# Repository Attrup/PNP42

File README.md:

# PNP42
Custom parts and PCBs used in the PNP42 prototype. 

# See It In Action
Time lapse of the prototype assembling the test-PCB:

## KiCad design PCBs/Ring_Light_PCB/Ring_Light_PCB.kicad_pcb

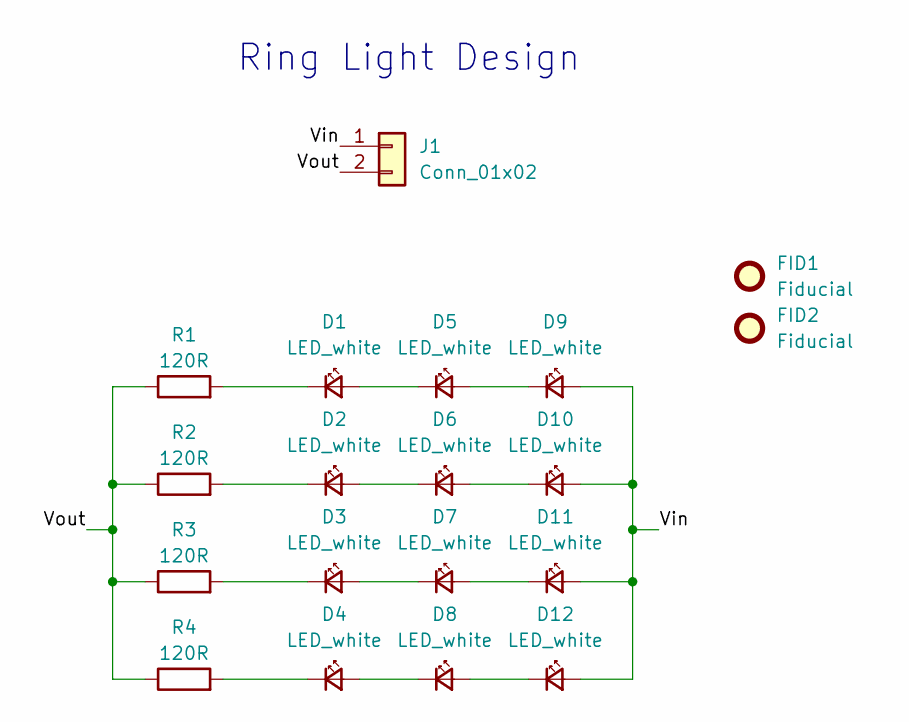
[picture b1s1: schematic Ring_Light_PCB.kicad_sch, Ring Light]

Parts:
D1, D2, D3, D4, D5, D6, D7, D8, D9, D10, D11, D12: LED_white; LED_D5.0mm
FID1, FID2: Fiducial; Fiducial_1mm_Mask2mm
J1: Conn_01x02; PinHeader_1x02_P2.54mm_Vertical
R1, R2, R3, R4: 120R; R_0805_2012Metric_Pad1.20x1.40mm_HandSolder

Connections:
/Vin: D9.2 (A), D10.2 (A), D11.2 (A), D12.2 (A), J1.1
/Vout: J1.2, R1.1, R2.1, R3.1, R4.1
unnamed: D1.1 (K), R1.2
unnamed: D1.2 (A), D5.1 (K)
unnamed: D2.1 (K), R2.2
unnamed: D2.2 (A), D6.1 (K)
unnamed: D3.1 (K), R3.2
unnamed: D3.2 (A), D7.1 (K)
unnamed: D4.1 (K), R4.2
unnamed: D4.2 (A), D8.1 (K)
unnamed: D5.2 (A), D9.1 (K)
unnamed: D6.2 (A), D10.1 (K)
unnamed: D7.2 (A), D11.1 (K)
unnamed: D8.2 (A), D12.1 (K)

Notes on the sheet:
Ring Light Design

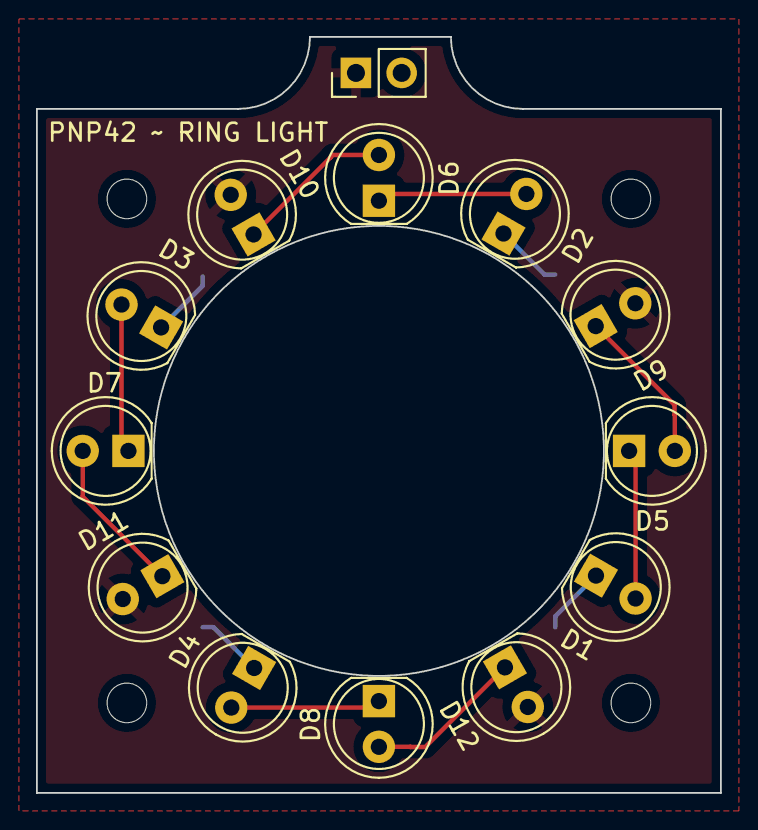
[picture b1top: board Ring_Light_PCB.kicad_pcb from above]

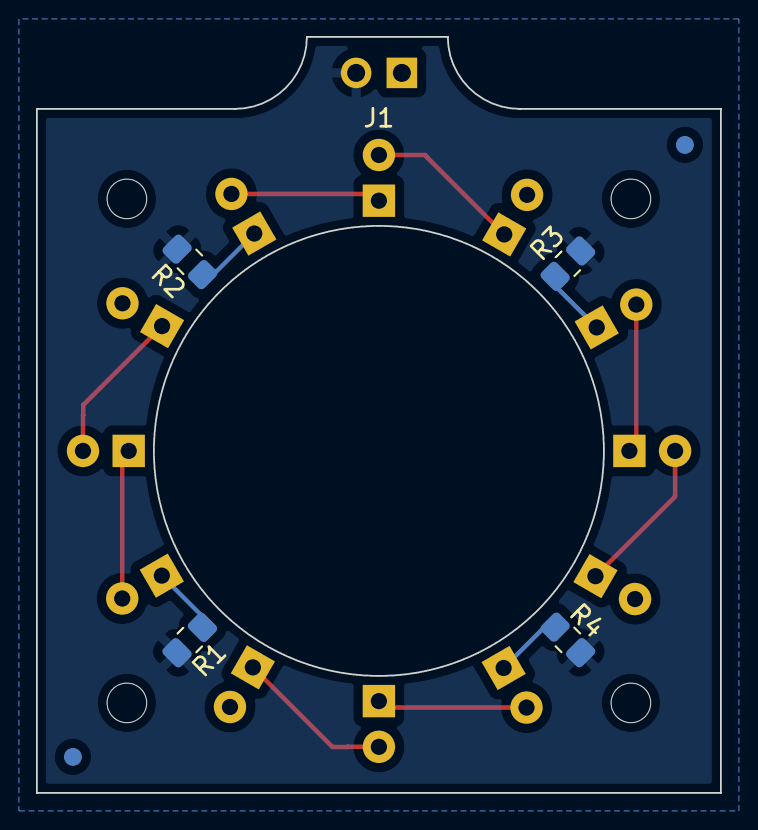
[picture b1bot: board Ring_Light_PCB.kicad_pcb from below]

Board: 2 copper layers, 38.0 x 42.0 mm, 19 parts (6 on the bottom side), 14 nets.

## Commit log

2022-06-15 Added Ring light PCB
2022-06-15 added 3d printed designs
2022-06-15 Added stl files for camera mounts
2022-06-15 Add machine, part and package config files
